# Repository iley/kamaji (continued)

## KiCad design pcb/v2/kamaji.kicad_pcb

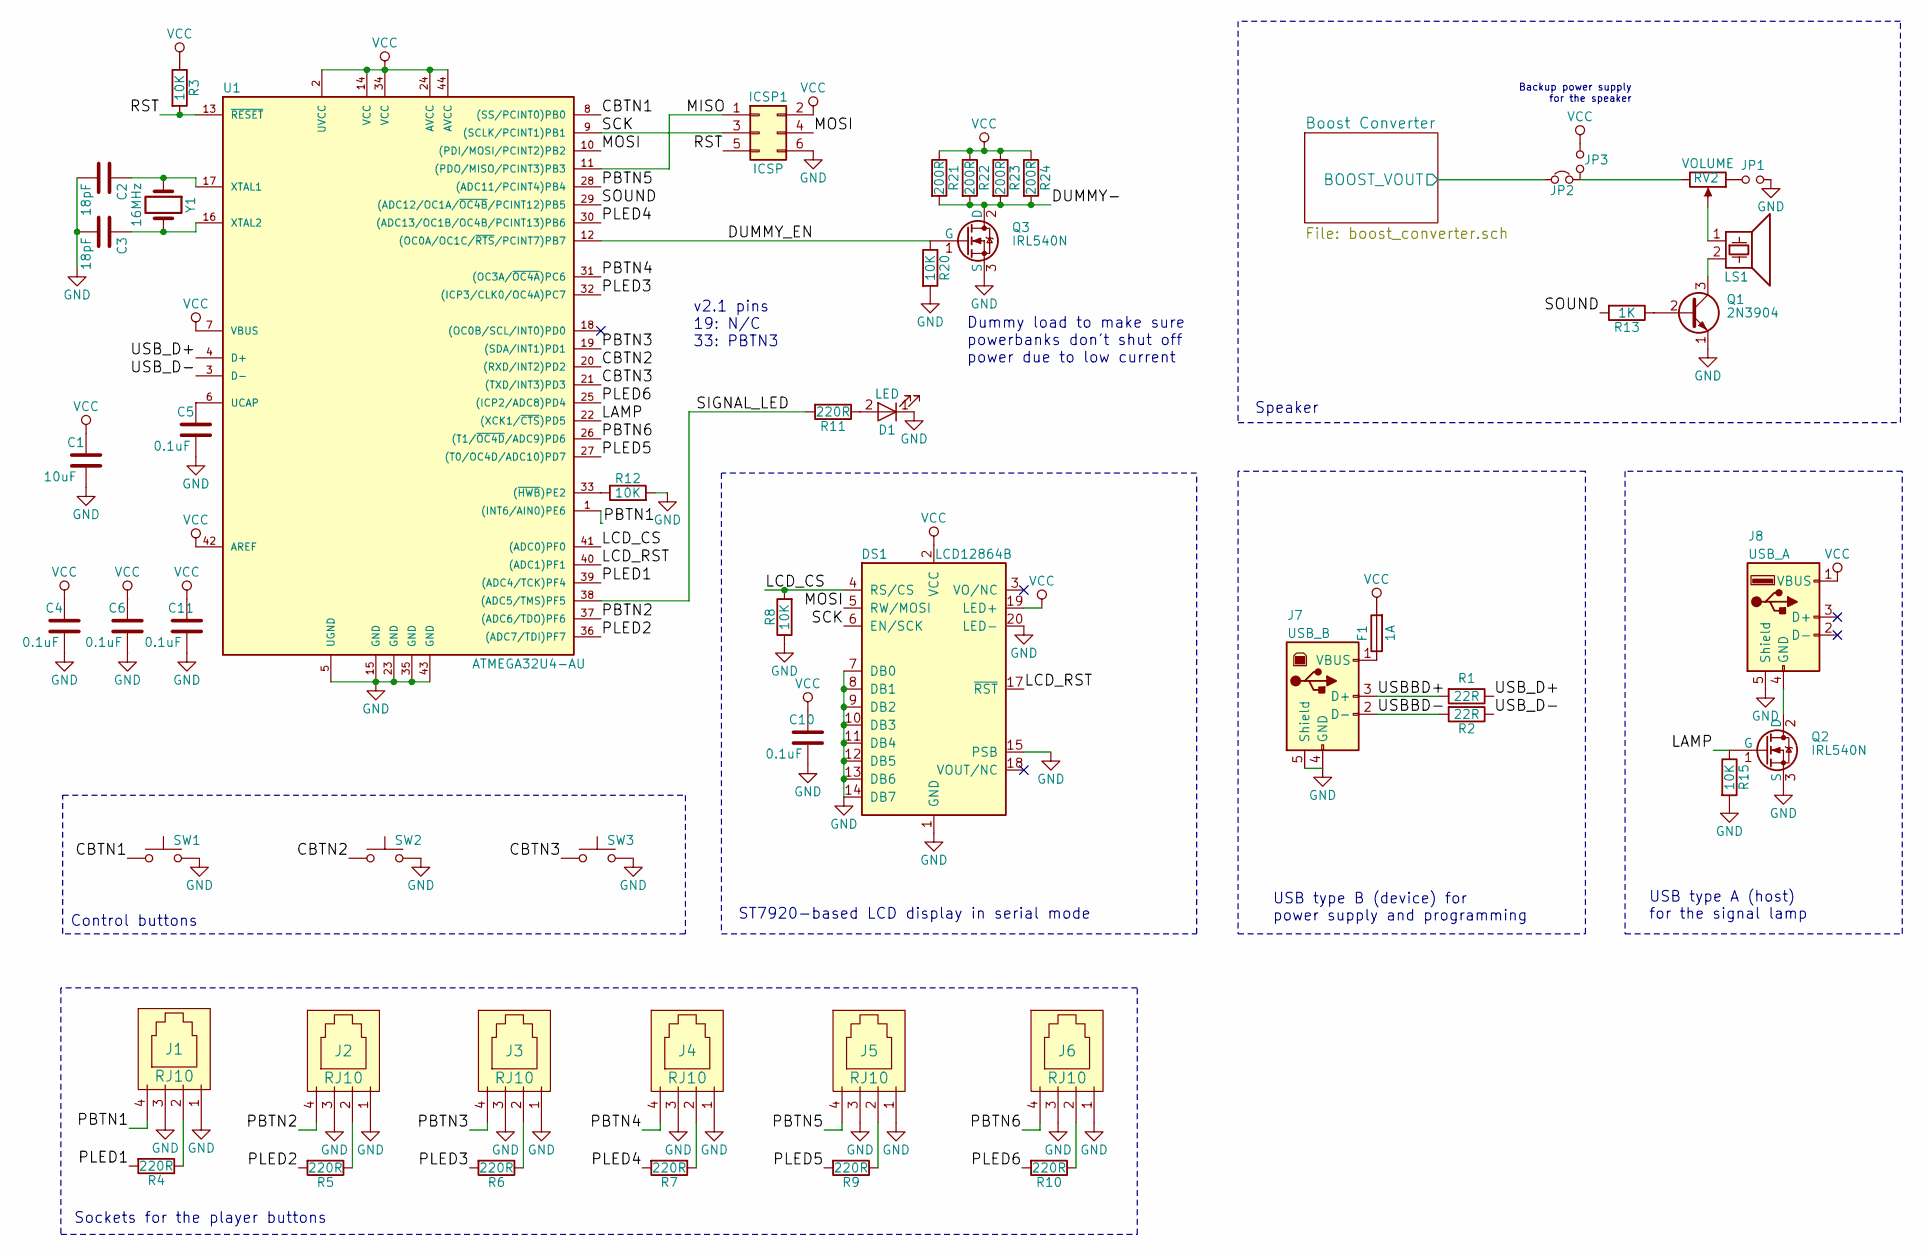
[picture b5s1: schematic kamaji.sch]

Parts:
C1: 10uF; C_1206_HandSoldering
C2, C3: 18pF; C_1206_HandSoldering
C4, C5, C6, C10, C11: 0.1uF; C_1206_HandSoldering
D1: LED; LED_D5.0mm
DS1: LCD12864B; LCD12864
F1: 1A; R_1812_HandSoldering
ICSP1: ICSP; ATmega_ISP_6pin
J1, J2, J3, J4, J5, J6: RJ10
J7: USB_B
J8: USB_A
JP1: Jumper_NO_Small; Pin_Header_Straight_1x02_Pitch2.54mm
JP2: Jumper_NC_Small; Pin_Header_Straight_1x02_Pitch2.54mm
JP3: SoundVcc2; Pin_Header_Straight_1x02_Pitch2.54mm
LS1: Speaker_Crystal; Buzzer_ARIO_98dB
Q1: 2N3904; TO-92_Molded_Narrow
Q2, Q3: IRL540N; TO-220-3_Horizontal
R1, R2: 22R; R_1206_HandSoldering
R3, R8, R12, R15, R20: 10K; R_1206_HandSoldering
R4, R5, R6, R7, R9, R10, R11: 220R; R_1206_HandSoldering
R13: 1K; R_1206_HandSoldering
R21, R22, R23, R24: 200R; R_Axial_DIN0207_L6.3mm_D2.5mm_P10.16mm_Horizontal
RV2: VOLUME; Potentiometer_Wheel_16mm
SW1, SW2, SW3: SW_Push; SW_PUSH-12mm_Wuerth-430476085716
U1: ATMEGA32U4-AU; TQFP-44_10x10mm_Pitch0.8mm
Y1: 16MHz; Crystal_HC49-U_Vertical

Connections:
/Boost Converter/BOOST_VOUT: JP2.1; also elsewhere on the board
/CBTN1: SW1.1, U1.8 ((SS/PCINT0)PB0)
/CBTN2: SW2.1, U1.20 ((RXD/INT2)PD2)
/CBTN3: SW3.1, U1.21 ((TXD/INT3)PD3)
/DUMMY-: Q3.2 (D), R21.2, R22.2, R23.2, R24.2
/DUMMY_EN: Q3.1 (G), R20.1, U1.12 ((OC0A/OC1C/~RTS~/PCINT7)PB7)
/LAMP: Q2.1 (G), R15.1, U1.22 ((XCK1/~CTS~)PD5)
/LCD_CS: DS1.4 (RS/CS), R8.2, U1.41 ((ADC0)PF0)
/LCD_RST: DS1.17 (~RST~), U1.40 ((ADC1)PF1)
/MISO: ICSP1.1, U1.11 ((PDO/MISO/PCINT3)PB3)
/MOSI: DS1.5 (RW/MOSI), ICSP1.4, U1.10 ((PDI/MOSI/PCINT2)PB2)
/PBTN1: J1.4, U1.1 ((INT6/AIN0)PE6)
/PBTN2: J2.4, U1.37 ((ADC6/TDO)PF6)
/PBTN3: J3.4, U1.19 ((SDA/INT1)PD1)
/PBTN4: J4.4, U1.31 ((OC3A/~OC4A~)PC6)
/PBTN5: J5.4, U1.28 ((ADC11/PCINT4)PB4)
/PBTN6: J6.4, U1.26 ((T1/~OC4D~/ADC9)PD6)
/PLED1: R4.2, U1.39 ((ADC4/TCK)PF4)
/PLED2: R5.2, U1.36 ((ADC7/TDI)PF7)
/PLED3: R6.2, U1.32 ((ICP3/CLK0/OC4A)PC7)
/PLED4: R7.2, U1.30 ((ADC13/OC1B/OC4B/PCINT13)PB6)
/PLED5: R9.2, U1.27 ((T0/OC4D/ADC10)PD7)
/PLED6: R10.2, U1.25 ((ICP2/ADC8)PD4)
/RST: ICSP1.5, R3.2, U1.13 (~RESET~)
/SCK: DS1.6 (EN/SCK), ICSP1.3, U1.9 ((SCLK/PCINT1)PB1)
/SIGNAL_LED: R11.2, U1.38 ((ADC5/TMS)PF5)
/SOUND: R13.2, U1.29 ((ADC12/OC1A/~OC4B~/PCINT12)PB5)
/USBBD+: J7.3 (D+), R1.2
/USBBD-: J7.2 (D-), R2.2
/USB_D+: R1.1, U1.4 (D+)
/USB_D-: R2.1, U1.3 (D-)
GND: C1.2, C2.2, C3.2, C4.2, C5.2, C6.2, C10.2, C11.2, D1.1 (K), DS1.1 (GND), DS1.7 (DB0), DS1.8 (DB1), DS1.9 (DB2), DS1.10 (DB3), DS1.11 (DB4), DS1.12 (DB5), DS1.13 (DB6), DS1.14 (DB7), DS1.15 (PSB), DS1.20 (LED-), ICSP1.6, J1.1, J1.3, J2.1, J2.3, J3.1, J3.3, J4.1, J4.3, J5.1, J5.3, J6.1, J6.3, J7.4 (GND), J7.5 (Shield), J8.5 (Shield), JP1.2, Q1.1 (E), Q2.3 (S), Q3.3 (S), R8.1, R12.2, R15.2, R20.2, SW1.2, SW2.2, SW3.2, U1.5 (UGND), U1.15 (GND), U1.23 (GND), U1.35 (GND), U1.43 (GND); also elsewhere on the board
unnamed: C2.1, U1.17 (XTAL1), Y1.1
unnamed: C3.1, U1.16 (XTAL2), Y1.2
unnamed: C5.1, U1.6 (UCAP)
unnamed: D1.2 (A), R11.1
unnamed: F1.1, J7.1 (VBUS)
unnamed: J1.2, R4.1
unnamed: J2.2, R5.1
unnamed: J3.2, R6.1
unnamed: J4.2, R7.1
unnamed: J5.2, R9.1
unnamed: J6.2, R10.1
unnamed: J8.4 (GND), Q2.2 (D)
unnamed: JP1.1, RV2.1
unnamed: JP2.2, JP3.2, RV2.3
unnamed: LS1.1, RV2.2
unnamed: LS1.2, Q1.3 (C)
unnamed: Q1.2 (B), R13.1
unnamed: R12.1, U1.33 ((~HWB~)PE2)
VCC: C1.1, C4.1, C6.1, C10.1, C11.1, DS1.2 (VCC), DS1.19 (LED+), F1.2, ICSP1.2, J8.1 (VBUS), JP3.1, R3.1, R21.1, R22.1, R23.1, R24.1, U1.2 (UVCC), U1.7 (VBUS), U1.14 (VCC), U1.24 (AVCC), U1.34 (VCC), U1.42 (AREF), U1.44 (AVCC); also elsewhere on the board

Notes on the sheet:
USB type B (device) for power supply and programming
USB type A (host) for the signal lamp
Backup power supply for the speaker
Dummy load to make sure powerbanks don't shut off power due to low current
ST7920-based LCD display in serial mode
Speaker
Sockets for the player buttons
Control buttons
v2.1 pins 19: N/C 33: PBTN3

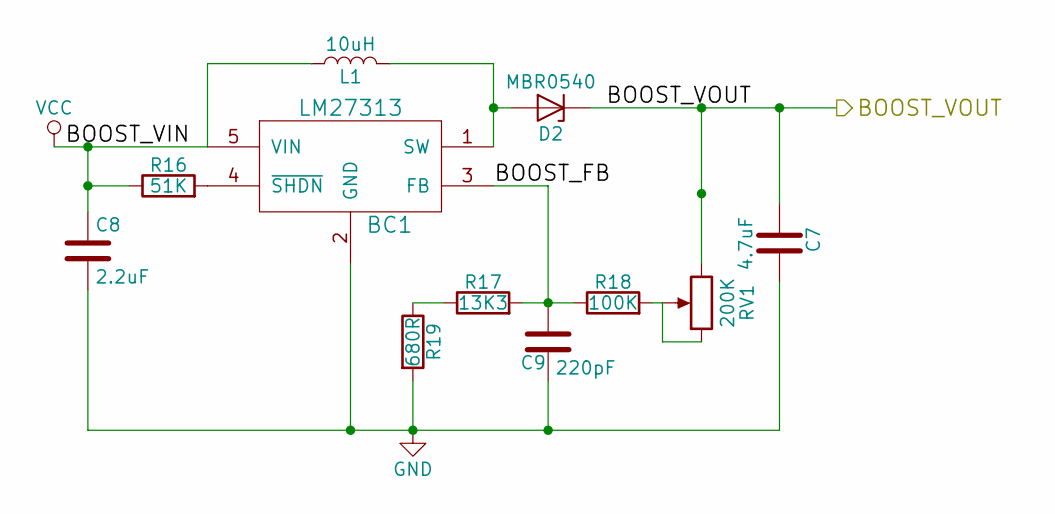
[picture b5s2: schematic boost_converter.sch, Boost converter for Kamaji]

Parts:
BC1: LM27313; SOT-23-5_HandSoldering
C7: 4.7uF; C_1206_HandSoldering
C8: 2.2uF; C_1206_HandSoldering
C9: 220pF; C_1206_HandSoldering
D2: MBR0540; D_SOD-323_HandSoldering
L1: 10uH; Inductor_PIS2408_SMD
R16: 51K; R_1206_HandSoldering
R17: 13K3; R_1206_HandSoldering
R18: 100K; R_1206_HandSoldering
R19: 680R; R_1206_HandSoldering
RV1: 200K; Potentiometer_Trimmer_Bourns_3339P_Horizontal

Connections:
/Boost Converter/BOOST_FB: BC1.3 (FB), C9.1, R17.2, R18.1
/Boost Converter/BOOST_VOUT: C7.1, D2.1 (K), RV1.3; also elsewhere on the board
GND: BC1.2 (GND), C7.2, C8.2, C9.2, R19.2; also elsewhere on the board
unnamed: BC1.1 (SW), D2.2 (A), L1.2
unnamed: BC1.4 (~SHDN), R16.2
unnamed: R17.1, R19.1
unnamed: R18.2, RV1.1, RV1.2
VCC: BC1.5 (VIN), C8.1, L1.1, R16.1; also elsewhere on the board

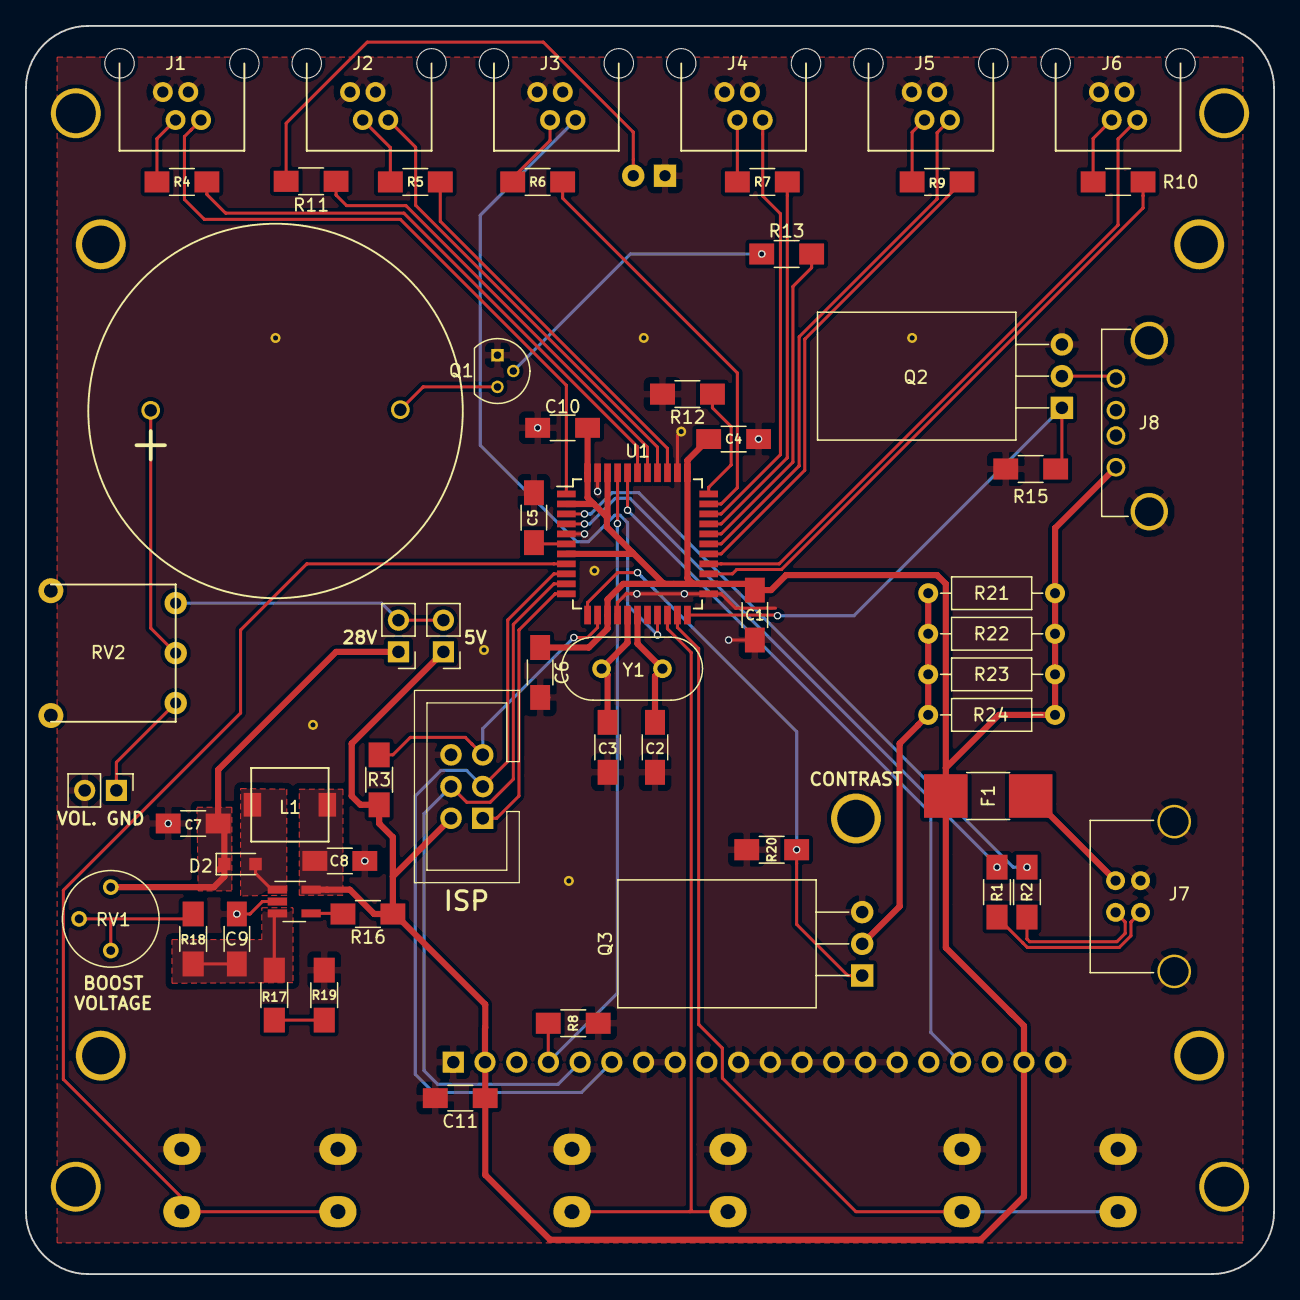
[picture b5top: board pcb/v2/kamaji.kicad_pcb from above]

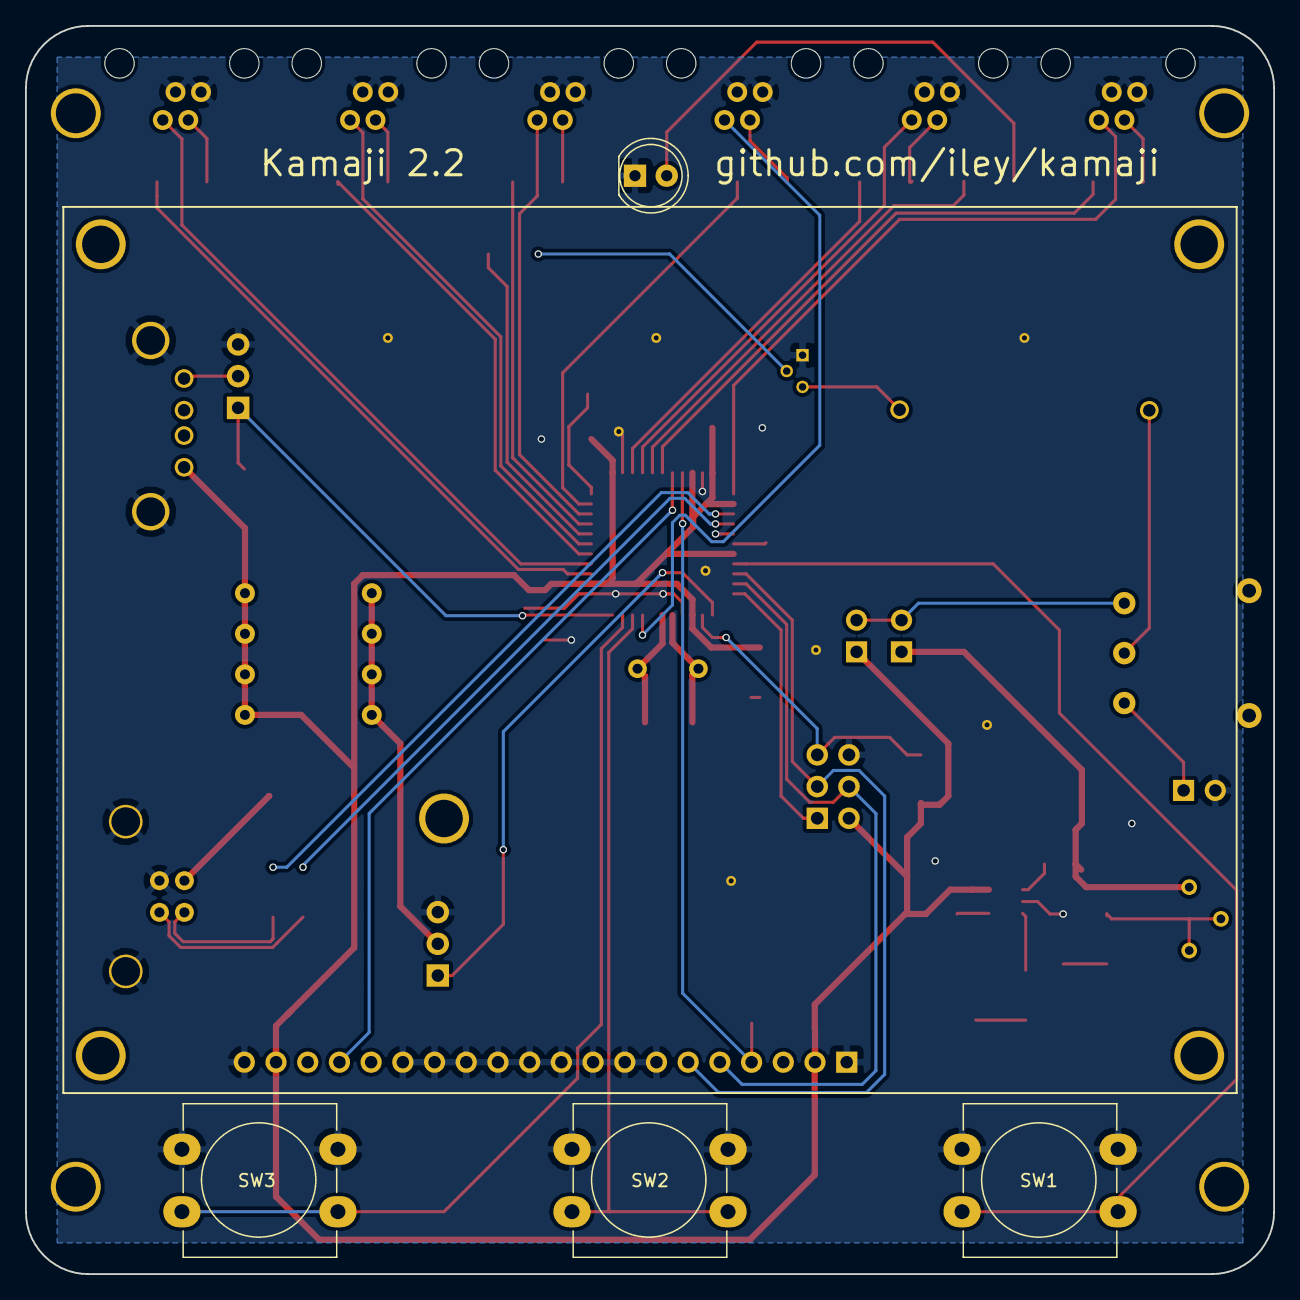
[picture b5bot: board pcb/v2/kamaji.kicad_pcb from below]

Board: 2 copper layers, 100.0 x 100.0 mm, 71 parts (5 on the bottom side), 56 nets.

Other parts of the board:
VIA**: Via_0.8mm
VIA**#2, VIA**#3, VIA**#4, VIA**#5, VIA**#6, VIA**#7, VIA**#8: Via_0.8mm

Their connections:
GND: VIA**.1, VIA**#2.1, VIA**#3.1, VIA**#4.1, VIA**#5.1, VIA**#6.1, VIA**#7.1, VIA**#8.1; also elsewhere on the board

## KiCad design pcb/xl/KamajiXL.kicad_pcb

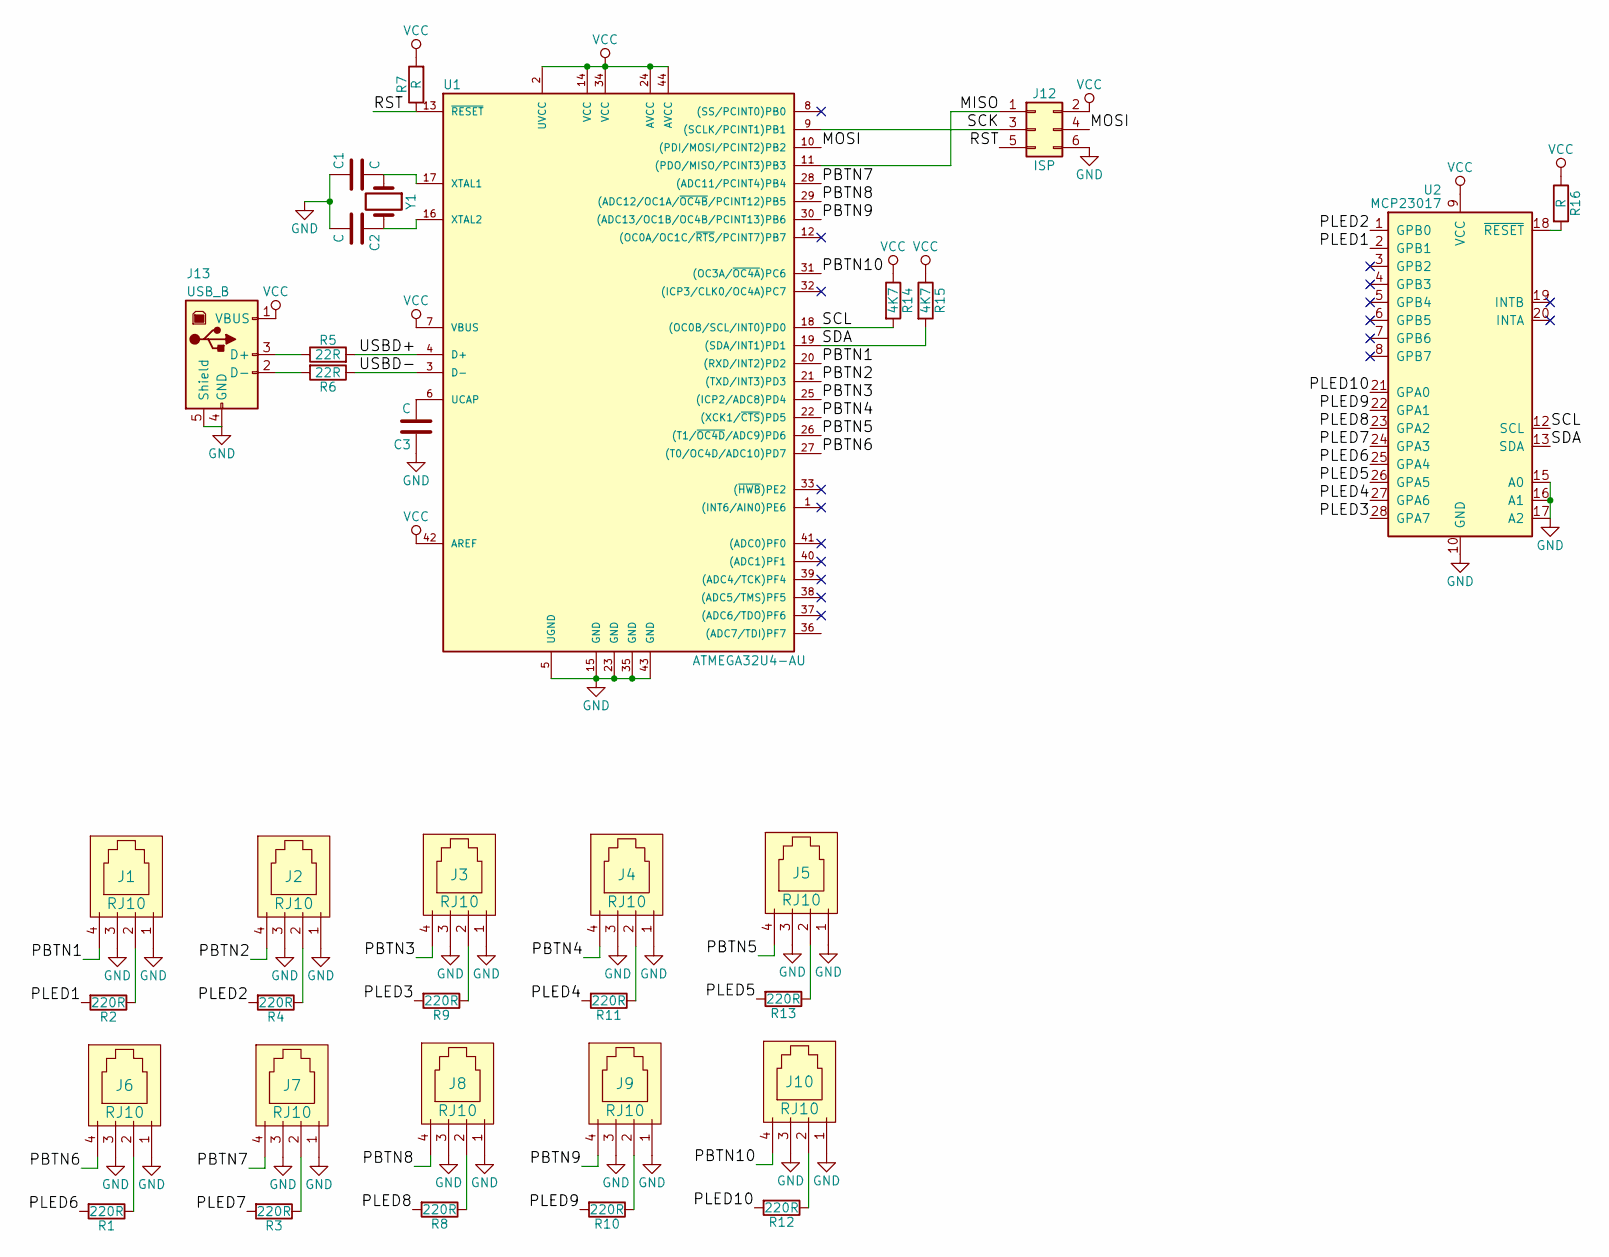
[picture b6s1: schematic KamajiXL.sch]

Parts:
C1, C2, C3: C; C_1206_HandSoldering
J1, J2, J3, J4, J5, J6, J7, J8, J9, J10: RJ10
J12: ISP; ATmega_ISP_6pin
J13: USB_B
R1, R2, R3, R4, R8, R9, R10, R11, R12, R13: 220R; R_1206_HandSoldering
R5, R6: 22R; R_1206_HandSoldering
R7, R16: R; R_1206_HandSoldering
R14, R15: 4K7; R_1206_HandSoldering
U1: ATMEGA32U4-AU; TQFP-44_10x10mm_Pitch0.8mm
U2: MCP23017; SOIC-28W_7.5x17.9mm_Pitch1.27mm
Y1: Crystal; Crystal_SMD_HC49-SD_HandSoldering

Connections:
/MISO: J12.1, U1.11 ((PDO/MISO/PCINT3)PB3)
/MOSI: J12.4, U1.10 ((PDI/MOSI/PCINT2)PB2)
/PBTN1: J1.4, U1.20 ((RXD/INT2)PD2)
/PBTN2: J2.4, U1.21 ((TXD/INT3)PD3)
/PBTN3: J3.4, U1.25 ((ICP2/ADC8)PD4)
/PBTN4: J4.4, U1.22 ((XCK1/~CTS~)PD5)
/PBTN5: J5.4, U1.26 ((T1/~OC4D~/ADC9)PD6)
/PBTN6: J6.4, U1.27 ((T0/OC4D/ADC10)PD7)
/PBTN7: J7.4, U1.28 ((ADC11/PCINT4)PB4)
/PBTN8: J8.4, U1.29 ((ADC12/OC1A/~OC4B~/PCINT12)PB5)
/PBTN9: J9.4, U1.30 ((ADC13/OC1B/OC4B/PCINT13)PB6)
/PBTN10: J10.4, U1.31 ((OC3A/~OC4A~)PC6)
/PLED1: R2.2, U2.2 (GPB1)
/PLED2: R4.2, U2.1 (GPB0)
/PLED3: R9.2, U2.28 (GPA7)
/PLED4: R11.2, U2.27 (GPA6)
/PLED5: R13.2, U2.26 (GPA5)
/PLED6: R1.2, U2.25 (GPA4)
/PLED7: R3.2, U2.24 (GPA3)
/PLED8: R8.2, U2.23 (GPA2)
/PLED9: R10.2, U2.22 (GPA1)
/PLED10: R12.2, U2.21 (GPA0)
/RST: J12.5, R7.1, U1.13 (~RESET~)
/SCK: J12.3, U1.9 ((SCLK/PCINT1)PB1)
/SCL: R14.2, U1.18 ((OC0B/SCL/INT0)PD0), U2.12 (SCL)
/SDA: R15.2, U1.19 ((SDA/INT1)PD1), U2.13 (SDA)
/USBD+: R5.2, U1.4 (D+)
/USBD-: R6.1, U1.3 (D-)
GND: C1.1, C2.2, C3.1, J1.1, J1.3, J2.1, J2.3, J3.1, J3.3, J4.1, J4.3, J5.1, J5.3, J6.1, J6.3, J7.1, J7.3, J8.1, J8.3, J9.1, J9.3, J10.1, J10.3, J12.6, J13.4 (GND), J13.5 (Shield), U1.5 (UGND), U1.15 (GND), U1.23 (GND), U1.35 (GND), U1.43 (GND), U2.10 (GND), U2.15 (A0), U2.16 (A1), U2.17 (A2)
unnamed: C1.2, U1.17 (XTAL1), Y1.1
unnamed: C2.1, U1.16 (XTAL2), Y1.2
unnamed: C3.2, U1.6 (UCAP)
unnamed: J1.2, R2.1
unnamed: J2.2, R4.1
unnamed: J3.2, R9.1
unnamed: J4.2, R11.1
unnamed: J5.2, R13.1
unnamed: J6.2, R1.1
unnamed: J7.2, R3.1
unnamed: J8.2, R8.1
unnamed: J9.2, R10.1
unnamed: J10.2, R12.1
unnamed: J13.2 (D-), R6.2
unnamed: J13.3 (D+), R5.1
unnamed: R16.2, U2.18 (~RESET)
VCC: J12.2, J13.1 (VBUS), R7.2, R14.1, R15.1, R16.1, U1.2 (UVCC), U1.7 (VBUS), U1.14 (VCC), U1.24 (AVCC), U1.34 (VCC), U1.42 (AREF), U1.44 (AVCC), U2.9 (VCC)

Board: 2 copper layers, 34 parts (0 on the bottom side), 46 nets, no tracks yet.

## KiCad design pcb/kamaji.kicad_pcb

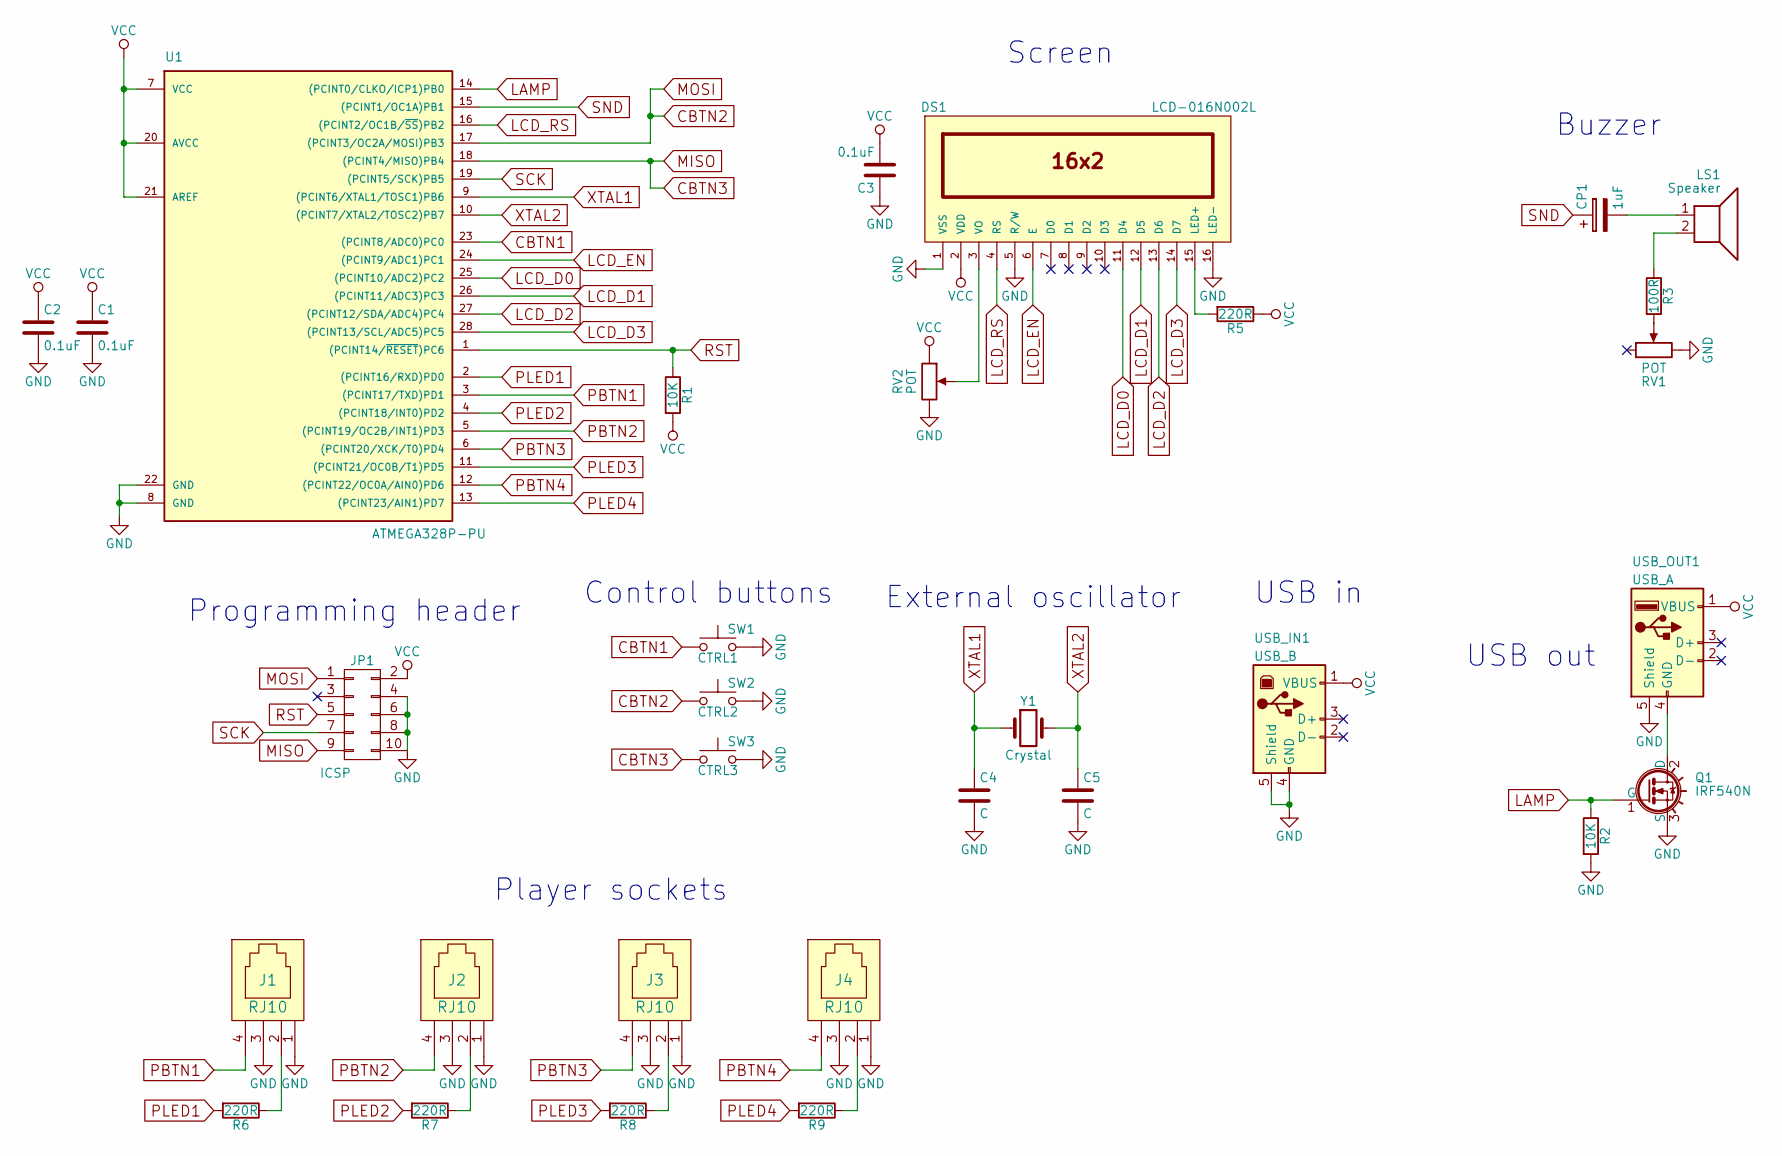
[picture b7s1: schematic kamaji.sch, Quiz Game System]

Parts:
C1, C2, C3: 0.1uF; C_Disc_D3.8mm_W2.6mm_P2.50mm
C4, C5: C; C_Disc_D3.8mm_W2.6mm_P2.50mm
CP1: 1uF; CP_Radial_D4.0mm_P1.50mm
DS1: LCD-016N002L; WC1602A
J1, J2, J3, J4: RJ10
JP1: ICSP; IDC_Header_Straight_10pins
LS1: Speaker; AL-30P
Q1: IRF540N; TO-220_Horizontal
R1, R2: 10K; R_Axial_DIN0207_L6.3mm_D2.5mm_P10.16mm_Horizontal
R3: 100R; R_Axial_DIN0207_L6.3mm_D2.5mm_P10.16mm_Horizontal
R5, R6, R7, R8, R9: 220R; R_Axial_DIN0207_L6.3mm_D2.5mm_P10.16mm_Horizontal
RV1, RV2: POT; Potentiometer_Triwood_RM-065
SW1: CTRL1; SW_PUSH_6mm_h8.5mm
SW2: CTRL2; SW_PUSH_6mm_h8.5mm
SW3: CTRL3; SW_PUSH_6mm_h8.5mm
U1: ATMEGA328P-PU; DIP-28_W7.62mm
USB_IN1: USB_B
USB_OUT1: USB_A
Y1: Crystal; Crystal_HC49-U_Vertical

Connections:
CBTN1: SW1.1, U1.23 ((PCINT8/ADC0)PC0)
CBTN2: JP1.1, SW2.1, U1.17 ((PCINT3/OC2A/MOSI)PB3)
CBTN3: JP1.9, SW3.1, U1.18 ((PCINT4/MISO)PB4)
GND: C1.2, C2.2, C3.1, C4.2, C5.2, DS1.1 (VSS), DS1.5 (R/W), DS1.16 (LED-), J1.1, J1.3, J2.1, J2.3, J3.1, J3.3, J4.1, J4.3, JP1.4, JP1.6, JP1.8, JP1.10, Q1.3 (S), R2.2, RV1.3, RV2.3, SW1.2, SW2.2, SW3.2, U1.8 (GND), U1.22 (GND), USB_IN1.4 (GND), USB_IN1.5 (Shield), USB_OUT1.5 (Shield)
LAMP: Q1.1 (G), R2.1, U1.14 ((PCINT0/CLKO/ICP1)PB0)
LCD_D0: DS1.11 (D4), U1.25 ((PCINT10/ADC2)PC2)
LCD_D1: DS1.12 (D5), U1.26 ((PCINT11/ADC3)PC3)
LCD_D2: DS1.13 (D6), U1.27 ((PCINT12/SDA/ADC4)PC4)
LCD_D3: DS1.14 (D7), U1.28 ((PCINT13/SCL/ADC5)PC5)
LCD_EN: DS1.6 (E), U1.24 ((PCINT9/ADC1)PC1)
LCD_RS: DS1.4 (RS), U1.16 ((PCINT2/OC1B/~SS~)PB2)
unnamed: CP1.2, LS1.1
unnamed: DS1.3 (VO), RV2.2
unnamed: DS1.15 (LED+), R5.2
unnamed: J1.2, R6.1
unnamed: J2.2, R7.1
unnamed: J3.2, R8.1
unnamed: J4.2, R9.1
unnamed: LS1.2, R3.1
unnamed: Q1.2 (D), USB_OUT1.4 (GND)
unnamed: R3.2, RV1.2
PBTN1: J1.4, U1.3 ((PCINT17/TXD)PD1)
PBTN2: J2.4, U1.5 ((PCINT19/OC2B/INT1)PD3)
PBTN3: J3.4, U1.6 ((PCINT20/XCK/T0)PD4)
PBTN4: J4.4, U1.12 ((PCINT22/OC0A/AIN0)PD6)
PLED1: R6.2, U1.2 ((PCINT16/RXD)PD0)
PLED2: R7.2, U1.4 ((PCINT18/INT0)PD2)
PLED3: R8.2, U1.11 ((PCINT21/OC0B/T1)PD5)
PLED4: R9.2, U1.13 ((PCINT23/AIN1)PD7)
RST: JP1.5, R1.1, U1.1 ((PCINT14/~RESET~)PC6)
SCK: JP1.7, U1.19 ((PCINT5/SCK)PB5)
SND: CP1.1, U1.15 ((PCINT1/OC1A)PB1)
VCC: C1.1, C2.1, C3.2, DS1.2 (VDD), JP1.2, R1.2, R5.1, RV2.1, U1.7 (VCC), U1.20 (AVCC), U1.21 (AREF), USB_IN1.1 (VBUS), USB_OUT1.1 (VBUS)
XTAL1: C4.1, U1.9 ((PCINT6/XTAL1/TOSC1)PB6), Y1.1
XTAL2: C5.1, U1.10 ((PCINT7/XTAL2/TOSC2)PB7), Y1.2

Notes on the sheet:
Buzzer
Player sockets
USB out
Control buttons
Programming header
USB in
Screen
External oscillator

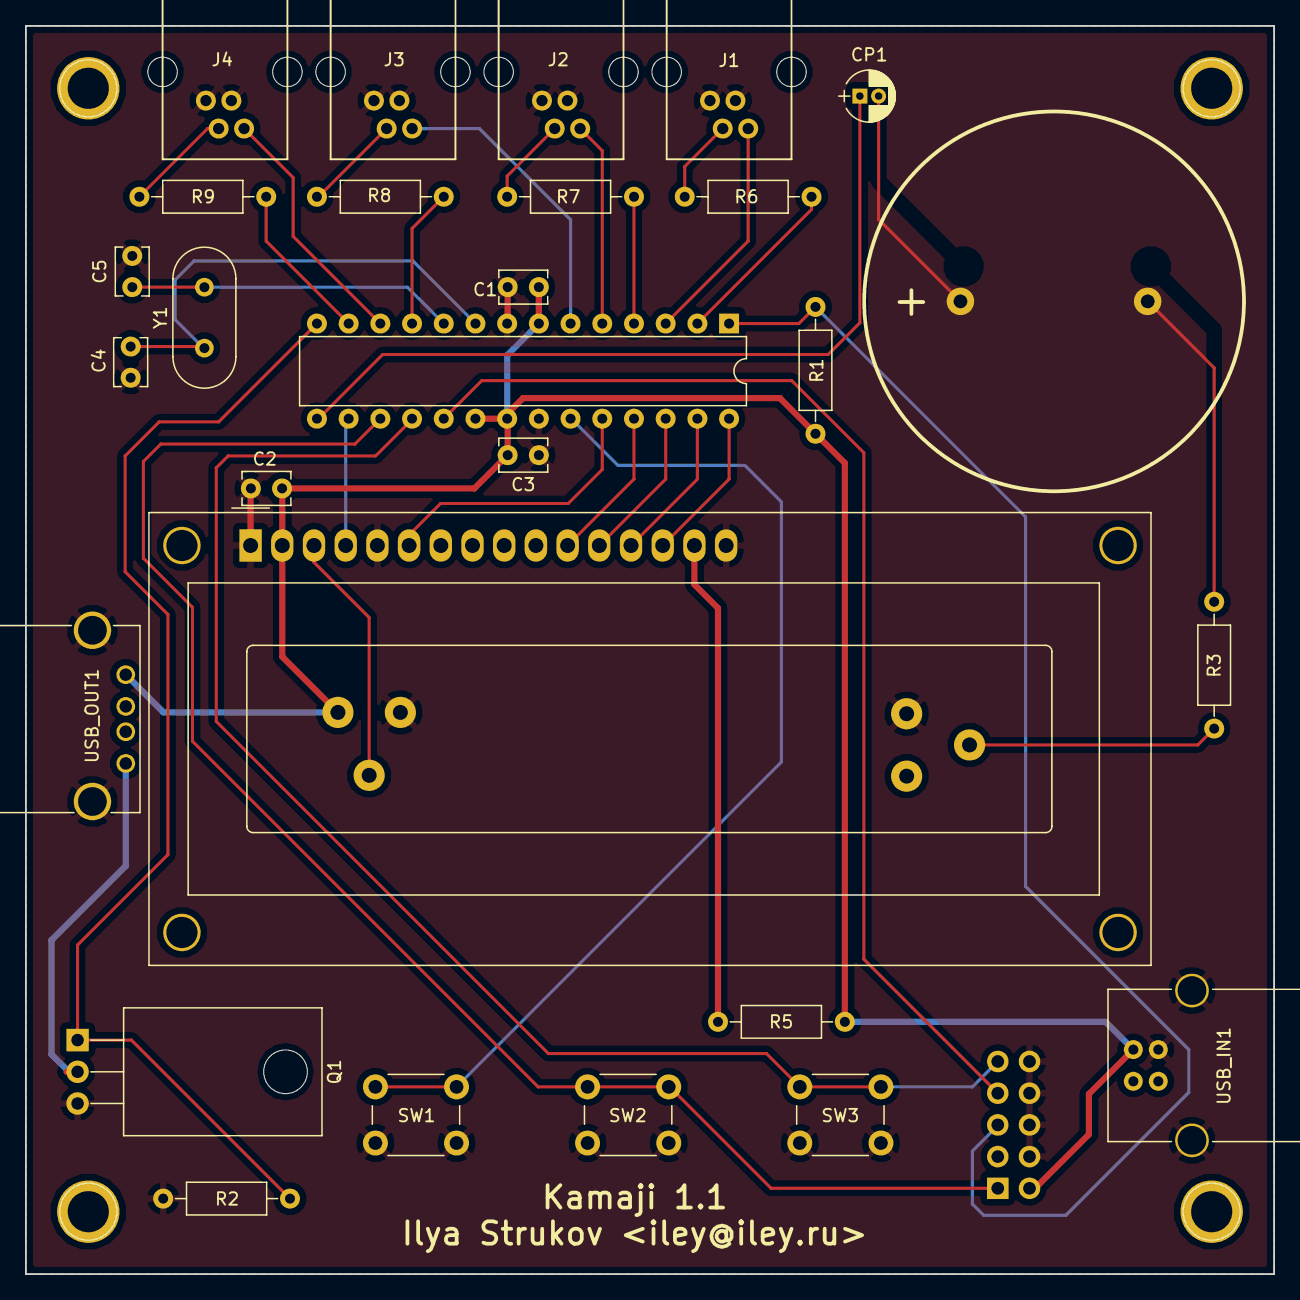
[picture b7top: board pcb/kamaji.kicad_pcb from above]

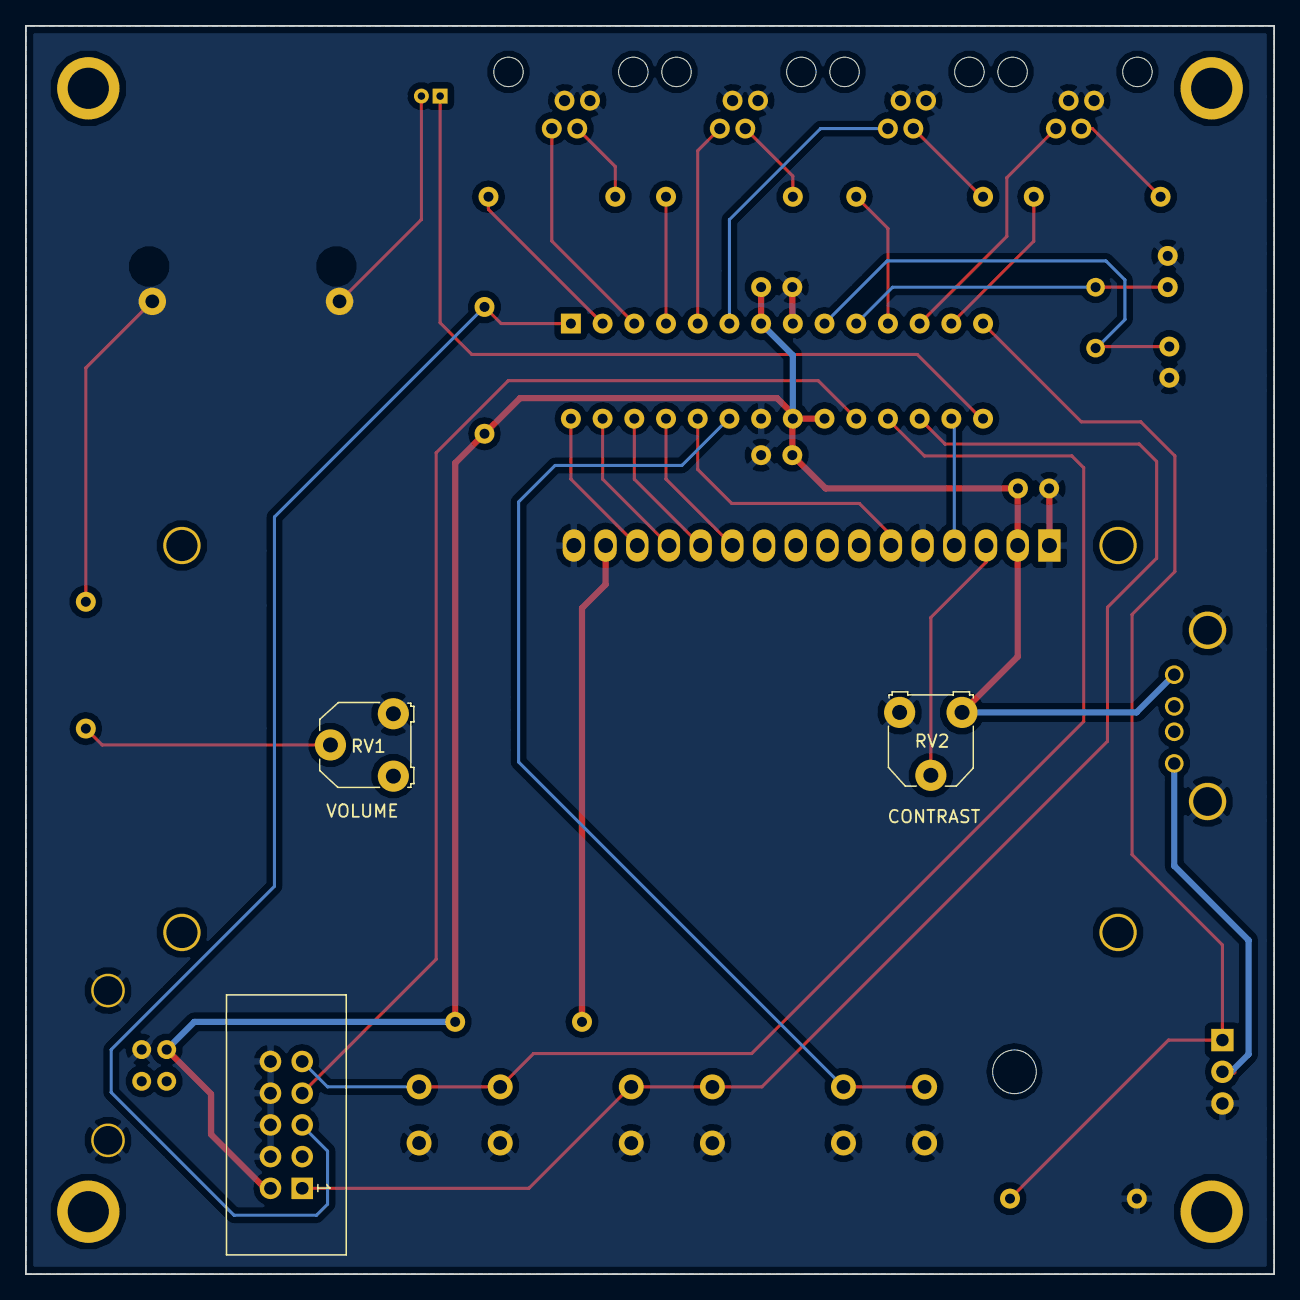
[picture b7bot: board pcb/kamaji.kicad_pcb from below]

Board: 2 copper layers, 100.0 x 100.0 mm, 31 parts (3 on the bottom side), 35 nets.

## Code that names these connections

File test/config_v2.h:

#ifndef CONFIG_V2_H
#define CONFIG_V2_H

#define USE_GRAPHIC_LCD 1
#define XPINS_ATMEGA32U4 1
#define USE_DUMMY_LOAD 1
#define USE_SIGNAL_LED 1
#define RUSSIAN
#define USE_LAMP 1
// TODO: Enable the lamp.

// All available buttons.
enum {
  BUTTON_PLAYER_1,
  BUTTON_PLAYER_2,
  BUTTON_PLAYER_3,
  BUTTON_PLAYER_4,
  BUTTON_PLAYER_5,
  BUTTON_PLAYER_6,

  BUTTON_CONTROL_1,
  BUTTON_CONTROL_2,
  BUTTON_CONTROL_3,

  BUTTON_COUNT = BUTTON_CONTROL_3 + 1,

  BUTTON_RESET = BUTTON_CONTROL_1,
  BUTTON_START = BUTTON_CONTROL_3,

  FIRST_PLAYER_BUTTON = BUTTON_PLAYER_1,
  LAST_PLAYER_BUTTON = BUTTON_PLAYER_6,
  PLAYER_COUNT = LAST_PLAYER_BUTTON - BUTTON_PLAYER_1 + 1
};

// Pin numbers for each button, indexed by the enum values above.
// Players (reversed):
// PBTN6: PD6 - pin 12
// PBTN5: PB4 - pin 8
// PBTN4: PC6 - pin 5
// PBTN3: PE2 - xpin 52
// PBTN2: PF6 - pin 19
// PBTN1: PE6 - pin 7
// Controls:
// CBTN1: PD3 - pin 1
// CBTN2: PD2 - pin 0
// CBTN3: PB0 - pin 17
#define DECLARE_KBUTTON_PINS()    \
  const uint8_t kButtonPins[] = {     \
    12, 8, 5, 52, 19, 7, /* players */ \
    1, 0, 17,      /* control */ \
  }

// Pin numbers for each player's LED, indexed by the buttons enum.
// E.g. kLedPins[BUTTON_PLAYER_1] is the first player's LED.
// Player LEDs (reversed):
// PLED6: PD4 - pin 4
// PLED5: PD7 - pin 6
// PLED4: PB6 - pin 10
// PLED3: PC7 - pin 13
// PLED2: PF7 - pin 18
// PLED1: PF4 - pin 21
#define DECLARE_KLED_PINS() \
  const uint8_t kLedPins[] = {4, 6, 10, 13, 18, 21}

#define DECLARE_KSPEAKER_PIN()  \
  const uint8_t kSpeakerPin = 9

// Lamp: PD5 - xpin 53
#define DECLARE_KLAMP_PIN()  \
  const uint8_t kLampPin = 53

// Dummy load: PB7 - pin 11
#define DECLARE_KDUMMY_PIN() \
  const uint8_t kDummyPin = 11

#define DECLARE_KSIGNAL_PIN() \
  const uint8_t kSignalPin = 20

#endif  // CONFIG_V2_H

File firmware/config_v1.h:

#ifndef CONFIG_V1_H
#define CONFIG_V1_H

#define USE_LAMP 1
#define XPINS_ATMEGA328P 1

// All available buttons.
enum {
  BUTTON_PLAYER_1,
  BUTTON_PLAYER_2,
  BUTTON_PLAYER_3,
  BUTTON_PLAYER_4,
  BUTTON_PLAYER_5,

  BUTTON_CONTROL_1,
  BUTTON_CONTROL_2,
  BUTTON_CONTROL_3,

  BUTTON_COUNT = BUTTON_CONTROL_3 + 1,

  BUTTON_RESET = BUTTON_CONTROL_1,
  BUTTON_START = BUTTON_CONTROL_3,

  FIRST_PLAYER_BUTTON = BUTTON_PLAYER_1,
  LAST_PLAYER_BUTTON = BUTTON_PLAYER_5,
  PLAYER_COUNT = BUTTON_PLAYER_5 - BUTTON_PLAYER_1 + 1
};

// Pin numbers for each button, indexed by the enum values above.
// Players:
// PBTN1: PD0 - pin 0
// PBTN2: PD2 - pin 2
// PBTN3: PD4 - pin 4
// PBTN4: PB7 - pin 51
// PBTN5: PD6 - pin 6
// Controls:
// CBTN1: PB2 - pin 10
// CBTN2: PB3 - pin 11
// CBTN3: PB4 - pin 12
#define DECLARE_KBUTTON_PINS()    \
  const int kButtonPins[] = {     \
    6, 51, 4, 2, 0, /* players */ \
    10, 11, 12,     /* control */ \
  }

// Pin numbers for each player's LED, indexed by the buttons enum.
// E.g. kLedPins[BUTTON_PLAYER_1] is the first player's LED.
// Player LEDs:
// PLED1: PD1 - pin 1
// PLED2: PD3 - pin 3
// PLED3: PB6 - pin 50
// PLED4: PD5 - pin 5
// PLED5: PD7 - pin 7
#define DECLARE_KLED_PINS() \
  const int kLedPins[] = {7, 5, 50, 3, 1}

#define DECLARE_KSPEAKER_PIN()  \
  const int kSpeakerPin = 9

// Lamp: PB0 - pin 8
#define DECLARE_KLAMP_PIN()  \
  const int kLampPin = 8

#endif  // CONFIG_V1_H
